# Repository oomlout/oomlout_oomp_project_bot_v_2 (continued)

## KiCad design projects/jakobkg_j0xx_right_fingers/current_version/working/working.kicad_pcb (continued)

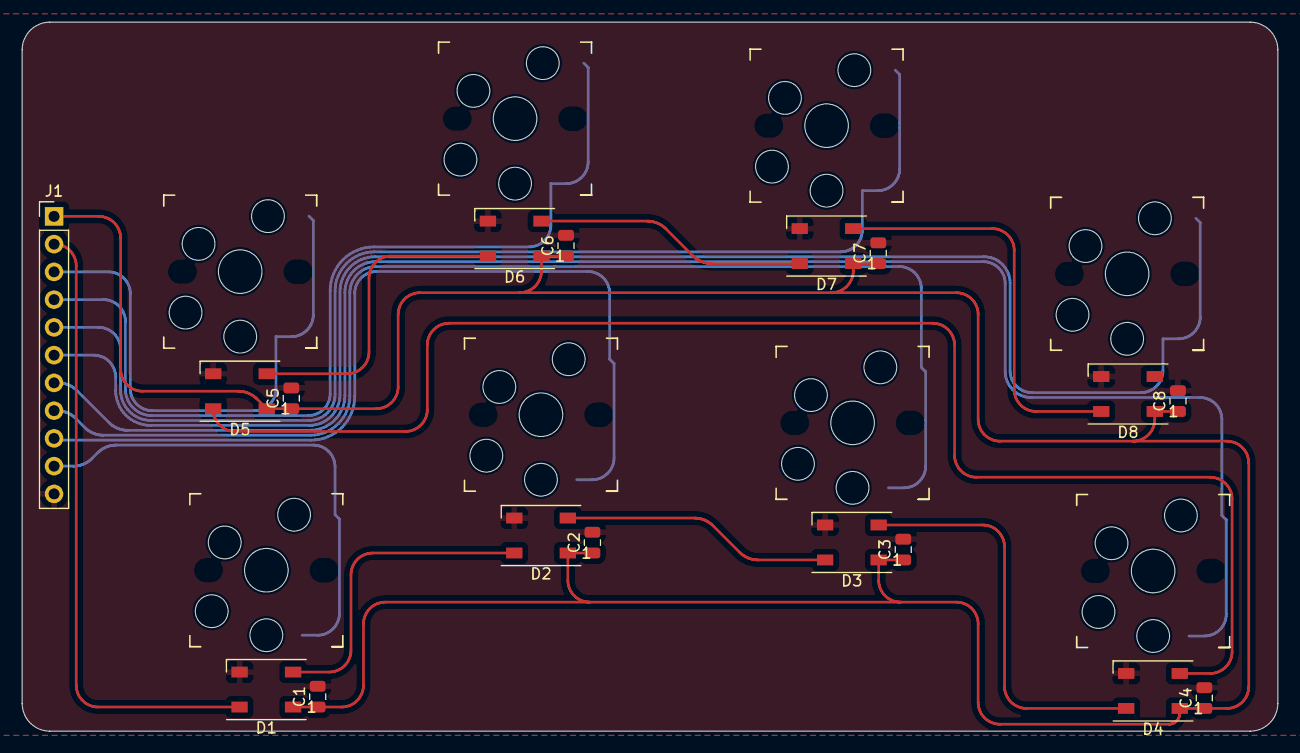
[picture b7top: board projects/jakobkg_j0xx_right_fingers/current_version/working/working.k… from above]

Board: 2 copper layers, 114.9 x 64.9 mm, 25 parts (0 on the bottom side), 18 nets.
